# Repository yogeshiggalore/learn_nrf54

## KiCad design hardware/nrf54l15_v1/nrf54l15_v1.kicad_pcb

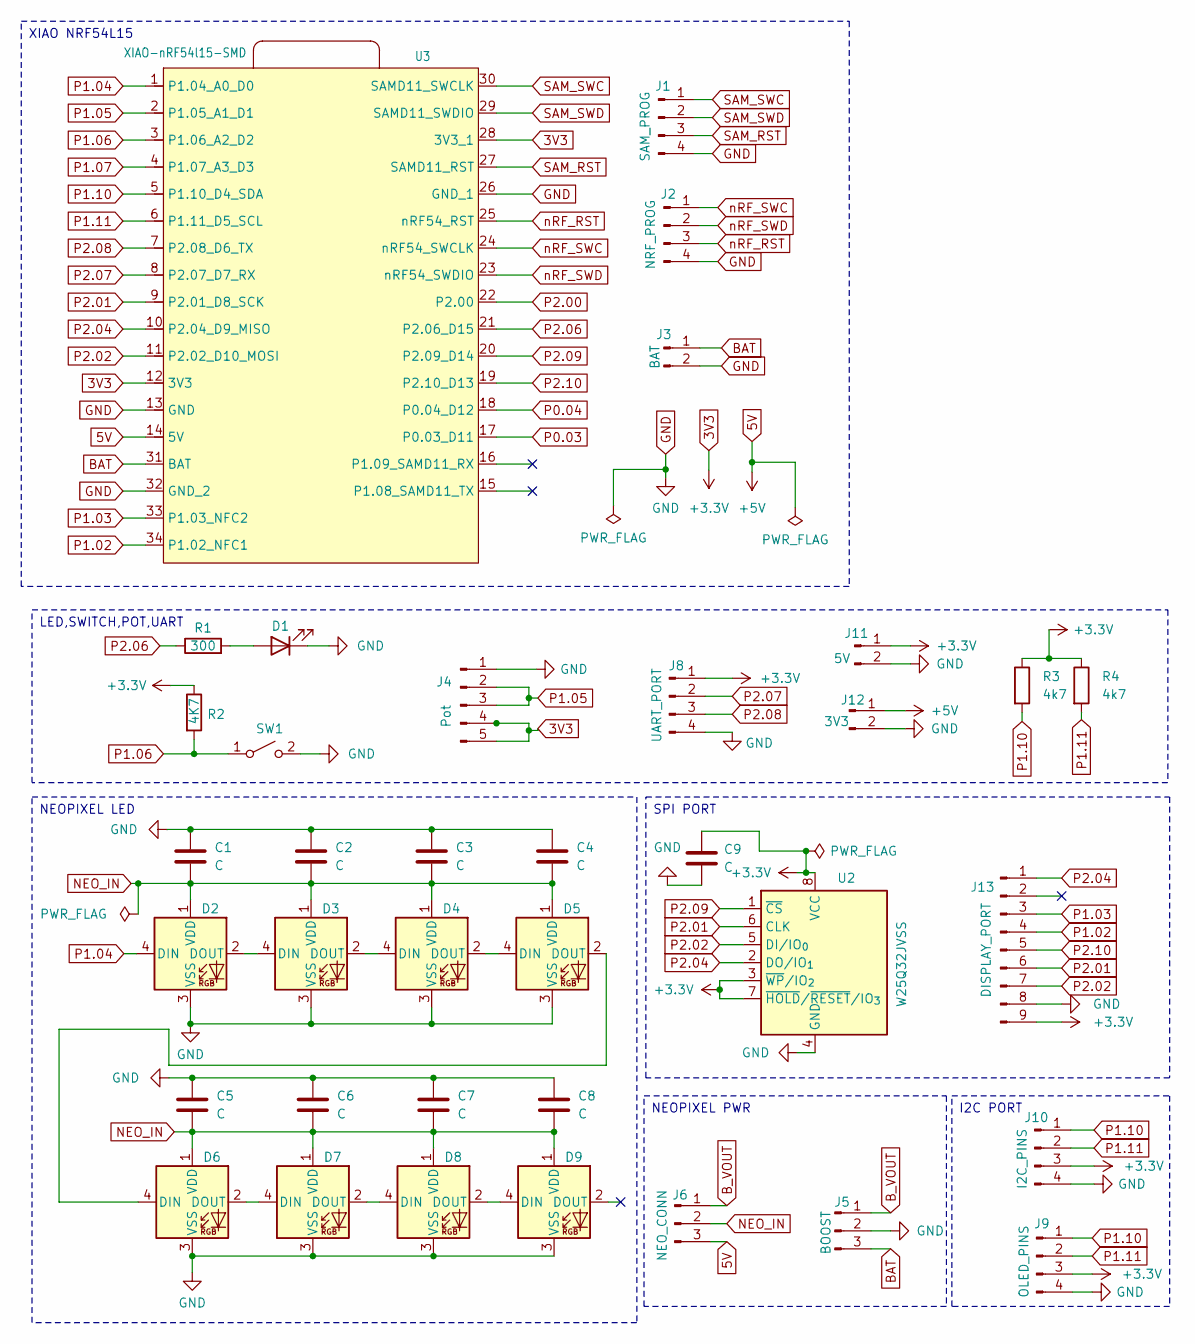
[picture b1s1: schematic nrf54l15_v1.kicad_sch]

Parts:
C1, C2, C3, C4, C5, C6, C7, C8, C9: C; C_0805_2012Metric_Pad1.18x1.45mm_HandSolder
D1: LED; LED_0805_2012Metric_Pad1.15x1.40mm_HandSolder
D2, D3, D4, D5, D6, D7, D8, D9: WS2812B; LED_WS2812B_PLCC4_5.0x5.0mm_P3.2mm
J1: SAM_PROG; JST_XH_S4B-XH-A_1x04_P2.50mm_Horizontal
J2: NRF_PROG; JST_XH_S4B-XH-A_1x04_P2.50mm_Horizontal
J3: BAT; JST_XH_S2B-XH-A-1_1x02_P2.50mm_Horizontal
J4: Pot; PinSocket_1x05_P2.54mm_Vertical
J5: BOOST; PinSocket_1x03_P2.54mm_Vertical
J6: NEO_CONN; PinSocket_1x03_P2.54mm_Vertical
J8: UART_PORT; JST_XH_S4B-XH-A-1_1x04_P2.50mm_Horizontal
J9: OLED_PINS; PinHeader_1x04_P2.54mm_Vertical
J10: I2C_PINS; JST_XH_S4B-XH-A_1x04_P2.50mm_Horizontal
J11: 5V; JST_XH_S2B-XH-A-1_1x02_P2.50mm_Horizontal
J12: 3V3; JST_XH_S2B-XH-A-1_1x02_P2.50mm_Horizontal
J13: DISPLAY_PORT; JST_XH_S9B-XH-A-1_1x09_P2.50mm_Horizontal
R1: 300; R_0805_2012Metric_Pad1.20x1.40mm_HandSolder
R2: 4K7; R_0805_2012Metric_Pad1.20x1.40mm_HandSolder
R3, R4: 4k7; R_0805_2012Metric_Pad1.20x1.40mm_HandSolder
SW1: SW_SPST; SW_SPST_PTS647_Sx38
U2: W25Q32JVSS; SOIC-8_5.3x5.3mm_P1.27mm
U3: XIAO-nRF54l15-SMD; ym_

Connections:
3V3: C9.2, J4.4, J4.5, J8.1, J9.3, J10.3, J11.1, J13.9, R2.1, R3.1, R4.1, U2.3 (~WP/IO_{2}), U2.7 (~HOLD/~RESET/IO_{3}), U2.8 (VCC), U3.12 (3V3), U3.28 (3V3_1)
5V: J6.3, J12.1, U3.14 (5V)
BAT: J3.1, J5.3, U3.31 (BAT)
B_VOUT: J5.1, J6.1
GND: C1.1, C2.1, C3.1, C4.1, C5.1, C6.1, C7.1, C8.1, C9.1, D1.1 (K), D2.3 (VSS), D3.3 (VSS), D4.3 (VSS), D5.3 (VSS), D6.3 (VSS), D7.3 (VSS), D8.3 (VSS), D9.3 (VSS), J1.4, J2.4, J3.2, J4.1, J5.2, J8.4, J9.4, J10.4, J11.2, J12.2, J13.8, SW1.2 (B), U2.4 (GND), U3.13 (GND), U3.26 (GND_1), U3.32 (GND_2)
NEO_IN: C1.2, C2.2, C3.2, C4.2, C5.2, C6.2, C7.2, C8.2, D2.1 (VDD), D3.1 (VDD), D4.1 (VDD), D5.1 (VDD), D6.1 (VDD), D7.1 (VDD), D8.1 (VDD), D9.1 (VDD), J6.2
unnamed: D1.2 (A), R1.2
unnamed: D2.2 (DOUT), D3.4 (DIN)
unnamed: D3.2 (DOUT), D4.4 (DIN)
unnamed: D4.2 (DOUT), D5.4 (DIN)
unnamed: D5.2 (DOUT), D6.4 (DIN)
unnamed: D6.2 (DOUT), D7.4 (DIN)
unnamed: D7.2 (DOUT), D8.4 (DIN)
unnamed: D8.2 (DOUT), D9.4 (DIN)
P0.03: U3.17 (P0.03_D11)
P0.04: U3.18 (P0.04_D12)
P1.02: J13.4, U3.34 (P1.02_NFC1)
P1.03: J13.3, U3.33 (P1.03_NFC2)
P1.04: D2.4 (DIN), U3.1 (P1.04_A0_D0)
P1.05: J4.2, J4.3, U3.2 (P1.05_A1_D1)
P1.06: R2.2, SW1.1 (A), U3.3 (P1.06_A2_D2)
P1.07: U3.4 (P1.07_A3_D3)
P1.10: J9.1, J10.1, R3.2, U3.5 (P1.10_D4_SDA)
P1.11: J9.2, J10.2, R4.2, U3.6 (P1.11_D5_SCL)
P2.00: U3.22 (P2.00)
P2.01: J13.6, U2.6 (CLK), U3.9 (P2.01_D8_SCK)
P2.02: J13.7, U2.5 (DI/IO_{0}), U3.11 (P2.02_D10_MOSI)
P2.04: J13.1, U2.2 (DO/IO_{1}), U3.10 (P2.04_D9_MISO)
P2.06: R1.1, U3.21 (P2.06_D15)
P2.07: J8.2, U3.8 (P2.07_D7_RX)
P2.08: J8.3, U3.7 (P2.08_D6_TX)
P2.09: U2.1 (~CS), U3.20 (P2.09_D14)
P2.10: J13.5, U3.19 (P2.10_D13)
SAM_RST: J1.3, U3.27 (SAMD11_RST)
SAM_SWC: J1.1, U3.30 (SAMD11_SWCLK)
SAM_SWD: J1.2, U3.29 (SAMD11_SWDIO)
nRF_RST: J2.3, U3.25 (nRF54_RST)
nRF_SWC: J2.1, U3.24 (nRF54_SWCLK)
nRF_SWD: J2.2, U3.23 (nRF54_SWDIO)

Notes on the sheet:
I2C PORT
NEOPIXEL PWR
LED,SWITCH,POT,UART
NEOPIXEL LED
XIAO NRF54L15
SPI PORT

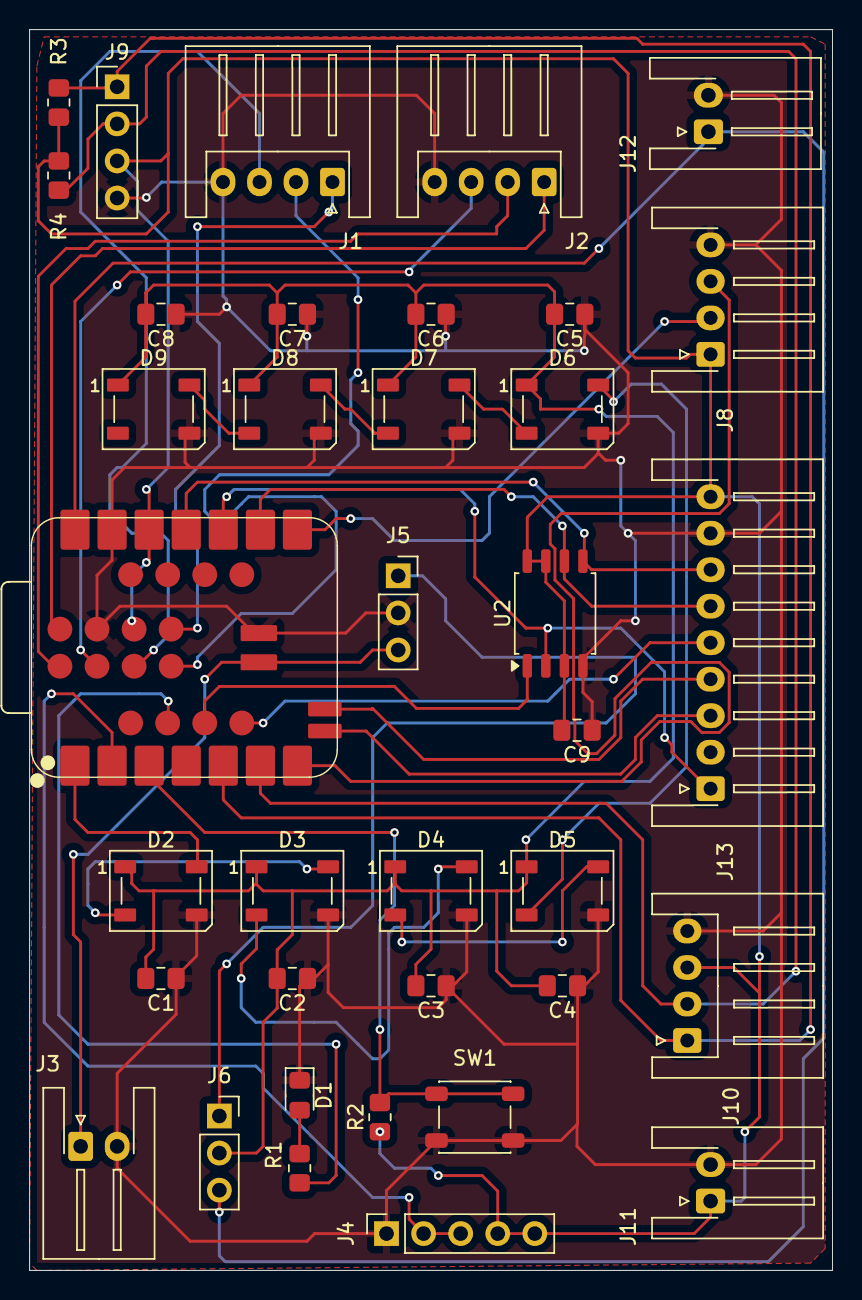
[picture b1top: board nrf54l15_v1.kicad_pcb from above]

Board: 2 copper layers, 55.0 x 85.0 mm, 37 parts (0 on the bottom side), 35 nets.

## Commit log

2025-10-08 init commit
    init commit
2025-10-08 init commit 2
    init commit 2
2025-10-10 added prink, i2c and uart
    added prink, i2c and uart
2025-10-14 added uart samples
    added uart samples
2025-10-28 samples push
    samples push
